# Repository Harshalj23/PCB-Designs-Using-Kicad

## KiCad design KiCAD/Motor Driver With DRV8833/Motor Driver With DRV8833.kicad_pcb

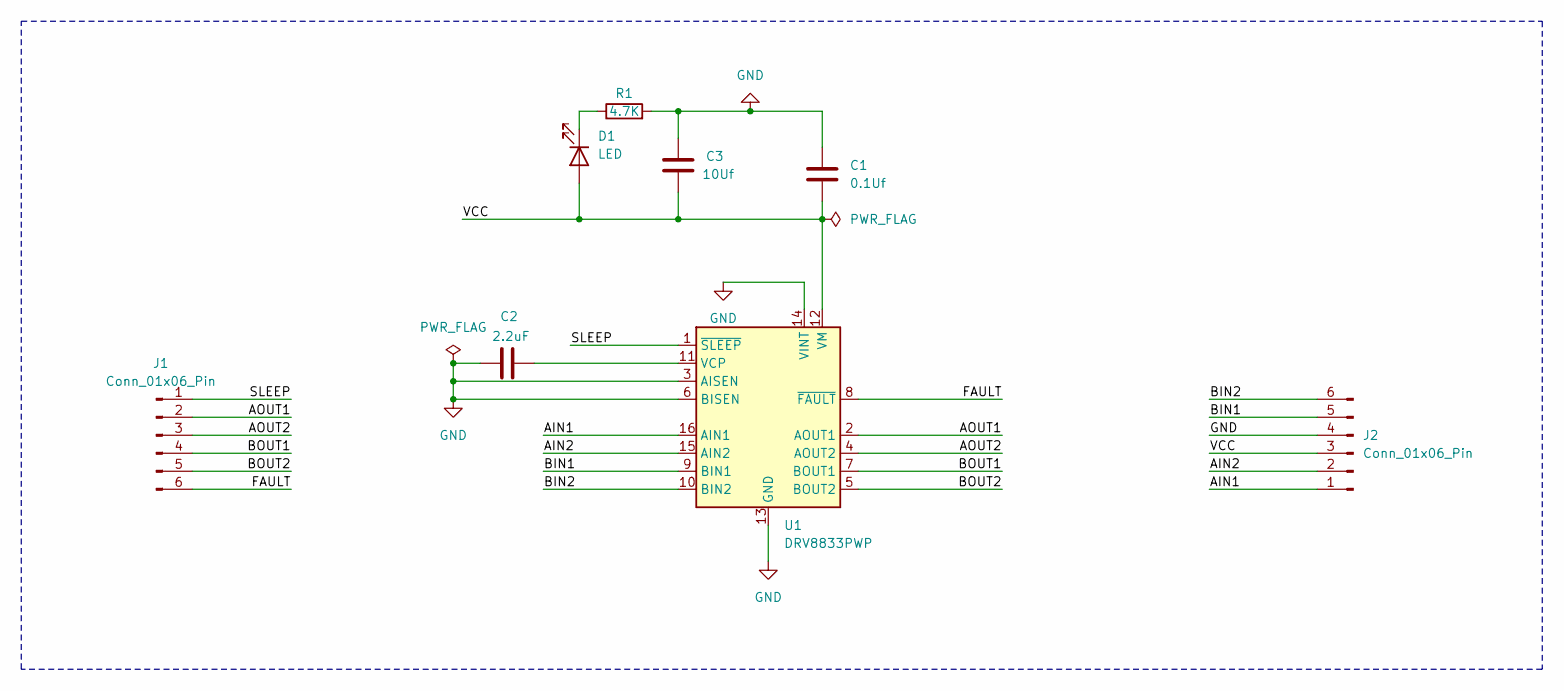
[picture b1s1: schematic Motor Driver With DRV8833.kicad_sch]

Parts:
C1: 0.1Uf; C_0805_2012Metric
C2: 2.2uF; C_0805_2012Metric
C3: 10Uf; CP_EIA-6032-20_AVX-F
D1: LED; LED_0805_2012Metric
J1, J2: Conn_01x06_Pin; PinHeader_1x06_P2.54mm_Vertical
R1: 4.7K; R_0805_2012Metric
U1: DRV8833PWP; HTSSOP-16-1EP_4.4x5mm_P0.65mm_EP3.4x5mm_Mask2.46x2.31mm_The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

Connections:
/AIN1: J2.1, U1.16 (AIN1)
/AIN2: J2.2, U1.15 (AIN2)
/AOUT1: J1.2, U1.2 (AOUT1)
/AOUT2: J1.3, U1.4 (AOUT2)
/BIN1: J2.5, U1.9 (BIN1)
/BIN2: J2.6, U1.10 (BIN2)
/BOUT1: J1.4, U1.7 (BOUT1)
/BOUT2: J1.5, U1.5 (BOUT2)
/FAULT: J1.6, U1.8 (~FAULT)
/SLEEP: J1.1, U1.1 (~SLEEP)
/VCC: C1.1, C3.1, D1.2 (A), J2.3, U1.12 (VM)
GND: C1.2, C2.2, C3.2, J2.4, R1.2, U1.3 (AISEN), U1.6 (BISEN), U1.13 (GND), U1.14 (VINT), U1.17 (GND)
unnamed: D1.1 (K), R1.1
unnamed: C2.1, U1.11 (VCP)

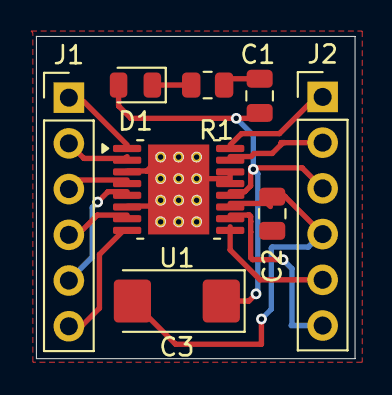
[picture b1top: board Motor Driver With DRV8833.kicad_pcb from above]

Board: 2 copper layers, 17.7 x 17.9 mm, 8 parts (0 on the bottom side), 14 nets.

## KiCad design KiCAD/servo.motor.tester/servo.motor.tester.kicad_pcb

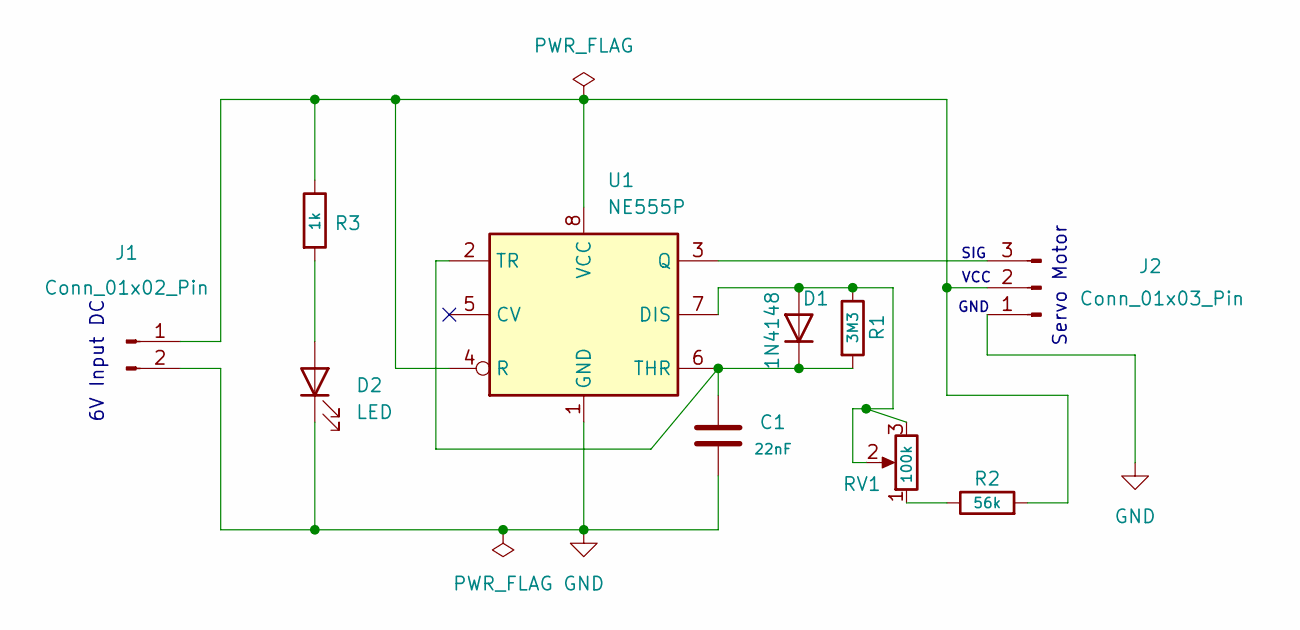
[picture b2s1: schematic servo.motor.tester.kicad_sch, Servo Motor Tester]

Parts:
C1: 22nF; C_Disc_D4.3mm_W1.9mm_P5.00mm
D1: 1N4148; D_DO-35_SOD27_P7.62mm_Horizontal
D2: LED; LED_D3.0mm
J1: Conn_01x02_Pin; PinHeader_1x02_P2.54mm_Horizontal
J2: Conn_01x03_Pin; PinHeader_1x03_P2.54mm_Horizontal
R1: 3M3; R_Axial_DIN0204_L3.6mm_D1.6mm_P7.62mm_Horizontal
R2: 56k; R_Axial_DIN0204_L3.6mm_D1.6mm_P7.62mm_Horizontal
R3: 1k; R_Axial_DIN0204_L3.6mm_D1.6mm_P7.62mm_Horizontal
RV1: 100k; Potentiometer_Alps_RK163_Single_Horizontal
U1: NE555P; DIP-8_W7.62mm

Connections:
GND: C1.1, D2.1 (K), J1.2, J2.1, U1.1 (GND)
unnamed: D1.2 (A), R1.1, RV1.2, RV1.3, U1.7 (DIS)
unnamed: C1.2, D1.1 (K), R1.2, U1.2 (TR), U1.6 (THR)
unnamed: D2.2 (A), R3.2
unnamed: J1.1, J2.2, R2.2, R3.1, U1.4 (R), U1.8 (VCC)
unnamed: J2.3, U1.3 (Q)
unnamed: R2.1, RV1.1

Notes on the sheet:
Servo Motor
SIG
VCC
GND
6V Input DC

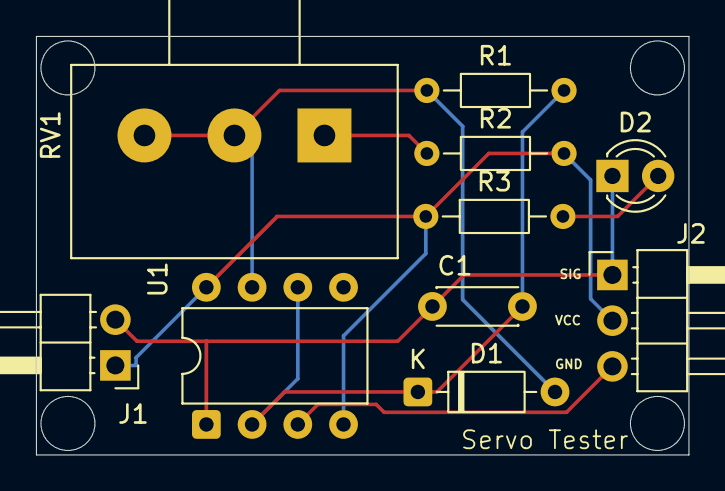
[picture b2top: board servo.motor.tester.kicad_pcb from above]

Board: 2 copper layers, 36.2 x 23.2 mm, 10 parts (0 on the bottom side), 7 nets.
